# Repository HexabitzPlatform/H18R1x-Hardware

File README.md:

# H18R1x-Hardware

Hexabitz Dual H-Bridge Motor Driver Module Hardware Design

Redesign this module using the STM32G0B1CEU6 MCU and STSPIN948. Use the EVSPIN948 as a reference.

This design must use three hexagons with a 2-layer PCB stack-up.

Schematic: 
PCB:

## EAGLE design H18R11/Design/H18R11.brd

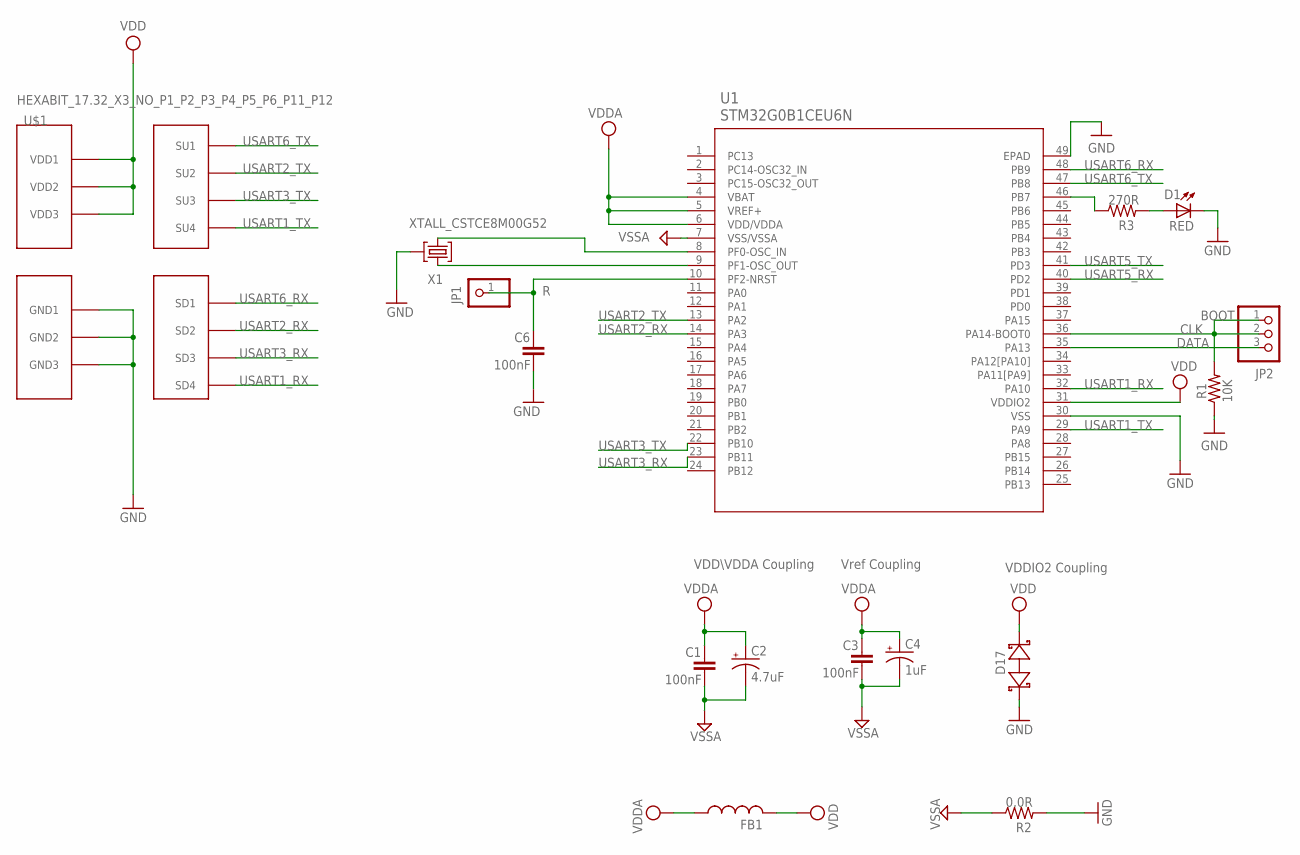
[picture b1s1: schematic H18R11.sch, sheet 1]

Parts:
C1, C3, C6: 100nF; C-0603
C2: 4.7uF; C-0805-POL
C4: 1uF; C-0805-POL
D1: RED; VLMS1300-GS08; MPN VLMS1300-GS08
D17: BOURNS_CDSOD323-T03SCBOURNS_CDSOD323-T03SC_0_0; BOURNS_CDSOD323-T03SC_0
FB1: FB-0603
JP1: R; 1X01
JP2: PINHD-1X3; 1X03
R1: 10K; R-0603
R2: 0.0R; R-0603
R3: 270R; R-0603
U1: STM32G0B1CEU6N; HEXABITZ_ICS_QFN_B1CEU6_STM-L
U$1: HEXABIT_17.32_X3_NO_P1_P2_P3_P4_P5_P6_P11_P12
X1: XTALL_CSTCE8M00G52

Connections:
CLK: JP2.1, JP2.2, R1.2, U1.36 (PA14-BOOT0)
DATA: JP2.3, U1.35 (PA13)
GND: C6.2, D1.C, D17.1 (A), R1.1, R2.2, U1.30 (VSS), U1.49 (EPAD), U$1.PAD_PD12 (GND1), U$1.PAD_PD17 (GND2), U$1.PAD_PD19 (GND3), X1.P$2 (2); also elsewhere on the board
unnamed: D1.A, R3.2
unnamed: R3.1, U1.46 (PB7)
unnamed: U1.9 (PF1-OSC_OUT), X1.P$1 (1)
unnamed: U1.8 (PF0-OSC_IN), X1.P$3 (3)
unnamed: C6.1, JP1.1, U1.10 (PF2-NRST)
USART1_RX: U1.32 (PA10), U$1.PAD_PD8 (SD4)
USART1_TX: U1.29 (PA9), U$1.PAD_PU8 (SU4)
USART2_RX: U1.14 (PA3), U$1.PAD_PD1 (SD2)
USART2_TX: U1.13 (PA2), U$1.PAD_PU1 (SU2)
USART3_RX: U1.23 (PB11), U$1.PAD_PD2 (SD3)
USART3_TX: U1.22 (PB10), U$1.PAD_PU2 (SU3)
USART5_RX: U1.40 (PD2)
USART5_TX: U1.41 (PD3)
USART6_RX: U1.48 (PB9), U$1.PAD_PD3 (SD1)
USART6_TX: U1.47 (PB8), U$1.PAD_PU3 (SU1)
VDD: D17.2 (C), FB1.2, U1.31 (VDDIO2), U$1.PAD_PU12 (VDD1), U$1.PAD_PU17 (VDD2), U$1.PAD_PU19 (VDD3); also elsewhere on the board
VDDA: C1.1, C2.1 (+), C3.1, C4.1 (+), FB1.1, U1.4 (VBAT), U1.5 (VREF+), U1.6 (VDD/VDDA)
VSSA: C1.2, C2.2 (-), C3.2, C4.2 (-), R2.1, U1.7 (VSS/VSSA); also elsewhere on the board

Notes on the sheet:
Vref Coupling
VDDIO2 Coupling
VDD\VDDA Coupling
BOOT

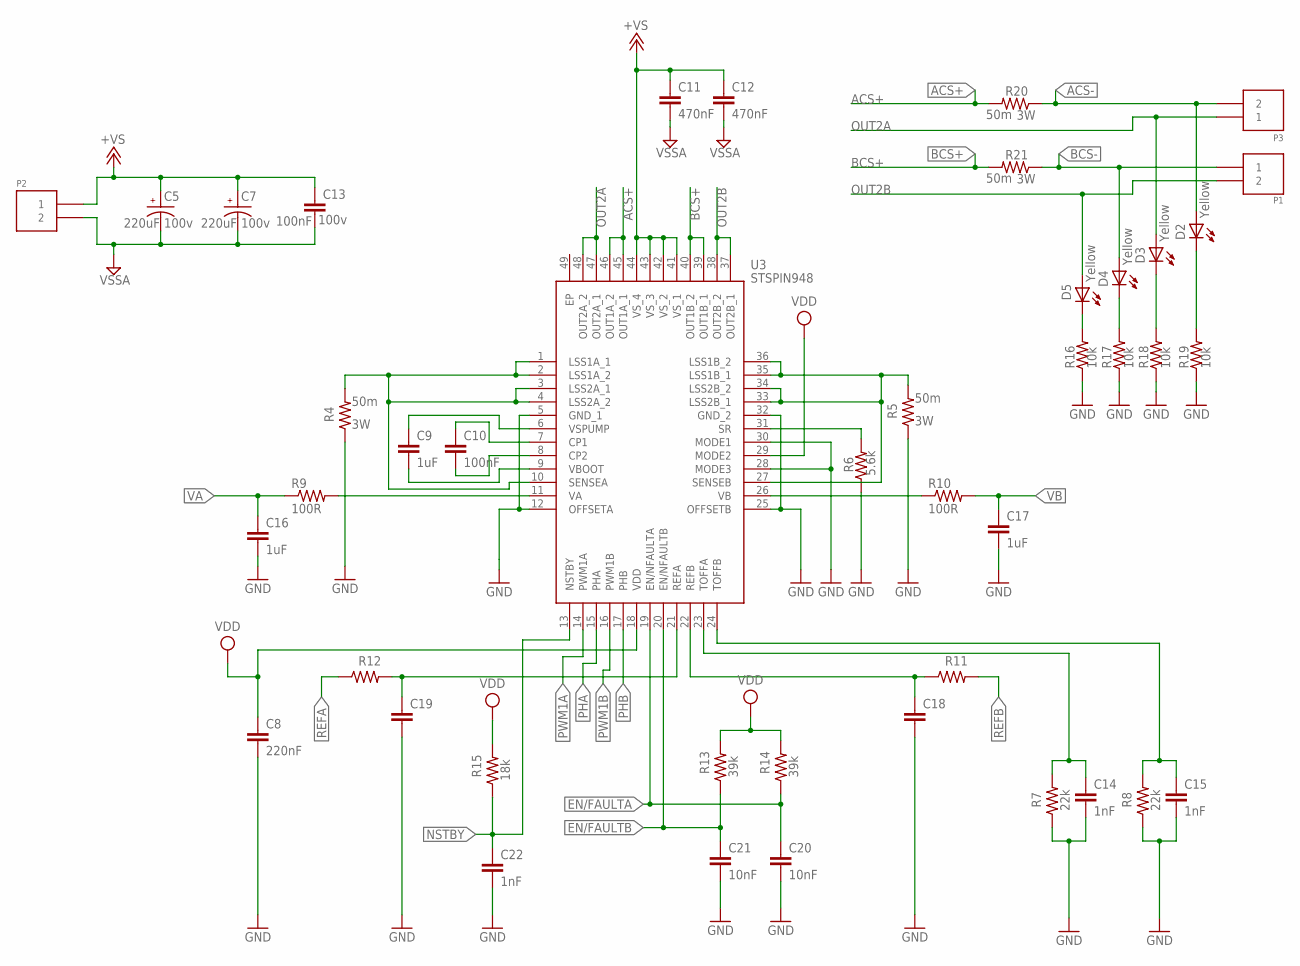
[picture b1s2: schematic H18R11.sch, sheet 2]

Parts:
C5, C7: 220uF; CAPPRD500W60D1250H2500
C8: 220nF; C-0603
C9, C16, C17: 1uF; C-0603
C10: 100nF; C-0603
C11, C12: 470nF; C-0603
C13: 100nF; C-0603; VOLTAGE_RATING 100v
C14, C15, C22: 1nF; C-0603
C18, C19: C-0603
C20, C21: 10nF; C-0603
D2: Yellow; VLMS1300-GS08; MPN VLMS1300-GS08
D3, D4, D5: Yellow; VLMS1300-GS08
P1, P2, P3: 1546111-2
R4, R5, R20, R21: 50m; R2512; MPN CRA2512-FZ-R050ELF
R6: 5.6k; R-0603
R7, R8: 22k; R-0603
R9, R10: 100R; R-0603
R11, R12: R-0603
R13, R14: 39k; R-0603
R15: 18k; R-0603
R16, R17, R18, R19: 10k; R-0805
U3: STSPIN948; QFN50P700X700X105-49N

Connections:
+VS: C5.P, C7.P, C11.1, C12.1, C13.1, P2.1, U3.41 (VS_1), U3.42 (VS_2), U3.43 (VS_3), U3.44 (VS_4)
ACS+: R20.2, U3.45 (OUT1A_1), U3.46 (OUT1A_2); also elsewhere on the board
ACS-: D2.A, P3.2, R20.1; also elsewhere on the board
BCS+: R21.2, U3.39 (OUT1B_1), U3.40 (OUT1B_2); also elsewhere on the board
BCS-: D4.A, P1.1, R21.1; also elsewhere on the board
EN/FAULTA: C20.1, R14.1, U3.19 (EN/NFAULTA)
EN/FAULTB: C21.1, R13.1, U3.20 (EN/NFAULTB)
GND: C8.2, C14.2, C15.2, C16.2, C17.2, C18.2, C19.2, C20.2, C21.2, C22.2, R4.1, R5.1, R6.1, R7.1, R8.1, R16.1, R17.1, R18.1, R19.1, U3.5 (GND_1), U3.12 (OFFSETA), U3.25 (OFFSETB), U3.28 (MODE3), U3.30 (MODE1), U3.32 (GND_2); also elsewhere on the board
unnamed: C9.1, U3.6 (VSPUMP)
unnamed: C9.2, U3.9 (VBOOT)
unnamed: C10.1, U3.7 (CP1)
unnamed: C10.2, U3.8 (CP2)
unnamed: R4.2, U3.1 (LSS1A_1), U3.2 (LSS1A_2), U3.3 (LSS2A_1), U3.4 (LSS2A_2), U3.10 (SENSEA)
unnamed: R5.2, U3.27 (SENSEB), U3.33 (LSS2B_1), U3.34 (LSS2B_2), U3.35 (LSS1B_1), U3.36 (LSS1B_2)
unnamed: R6.2, U3.31 (SR)
unnamed: C14.1, R7.2, U3.23 (TOFFA)
unnamed: R9.2, U3.11 (VA)
unnamed: R10.1, U3.26 (VB)
unnamed: C15.1, R8.2, U3.24 (TOFFB)
unnamed: C19.1, R12.2, U3.21 (REFA)
unnamed: C18.1, R11.1, U3.22 (REFB)
unnamed: D3.C, R18.2
unnamed: D5.C, R16.2
unnamed: D4.C, R17.2
unnamed: D2.C, R19.2
NSTBY: C22.1, R15.1, U3.13 (NSTBY)
OUT2A: D3.A, P3.1, U3.47 (OUT2A_1), U3.48 (OUT2A_2)
OUT2B: D5.A, P1.2, U3.37 (OUT2B_1), U3.38 (OUT2B_2)
PHA: U3.15 (PHA)
PHB: U3.17 (PHB)
PWM1A: U3.14 (PWM1A)
PWM1B: U3.16 (PWM1B)
REFA: R12.1
REFB: R11.2
VA: C16.1, R9.1
VB: C17.1, R10.2
VDD: C8.1, R13.2, R14.2, R15.2, U3.18 (VDD), U3.29 (MODE2); also elsewhere on the board
VSSA: C5.N, C7.N, C11.2, C12.2, C13.2, P2.2; also elsewhere on the board

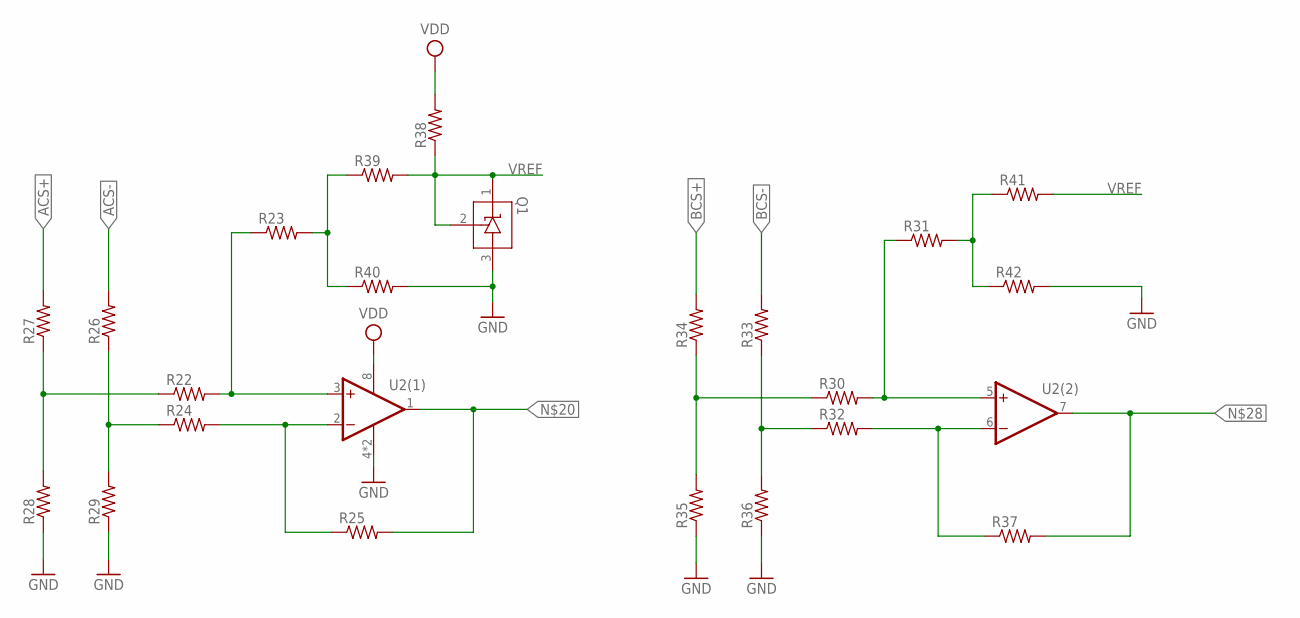
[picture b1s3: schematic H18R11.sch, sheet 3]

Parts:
Q1: TL431QDBZR,215; SOT23_TO-236AB_NEX
R22, R23, R24, R25, R26, R27, R28, R29, R30, R31, R32, R33, R34, R35, R36, R37, R38, R39, R40, R41, R42: R-0402
U2: TSV772IQ2T_SEPARATED_SYMBOLSSON50P200X200X60-9N; SON50P200X200X60-9N

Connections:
ACS+: R27.2; also elsewhere on the board
ACS-: R26.2; also elsewhere on the board
BCS+: R34.2; also elsewhere on the board
BCS-: R33.2; also elsewhere on the board
GND: Q1.3, R28.1, R29.1, R35.1, R36.1, R40.2, R42.2, U2.4 (V-), U2.9 (V-); also elsewhere on the board
unnamed: R25.2, U2.1 (OUT)
unnamed: R24.2, R25.1, U2.2 (-IN)
unnamed: R31.2, R41.1, R42.1
unnamed: R24.1, R26.1, R29.2
unnamed: R22.1, R27.1, R28.2
unnamed: R37.2, U2.7 (OUT)
unnamed: R32.2, R37.1, U2.6 (-IN)
unnamed: R32.1, R33.1, R36.2
unnamed: R30.1, R34.1, R35.2
unnamed: R22.2, R23.1, U2.3 (+IN)
unnamed: R23.2, R39.1, R40.1
VDD: R38.2, U2.8 (V+); also elsewhere on the board
VREF: Q1.1, Q1.2, R30.2, R31.1, R38.1, R39.2, R41.2, U2.5 (+IN)

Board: 4 copper layers, 82 parts (35 on the bottom side), 60 nets, no tracks yet.

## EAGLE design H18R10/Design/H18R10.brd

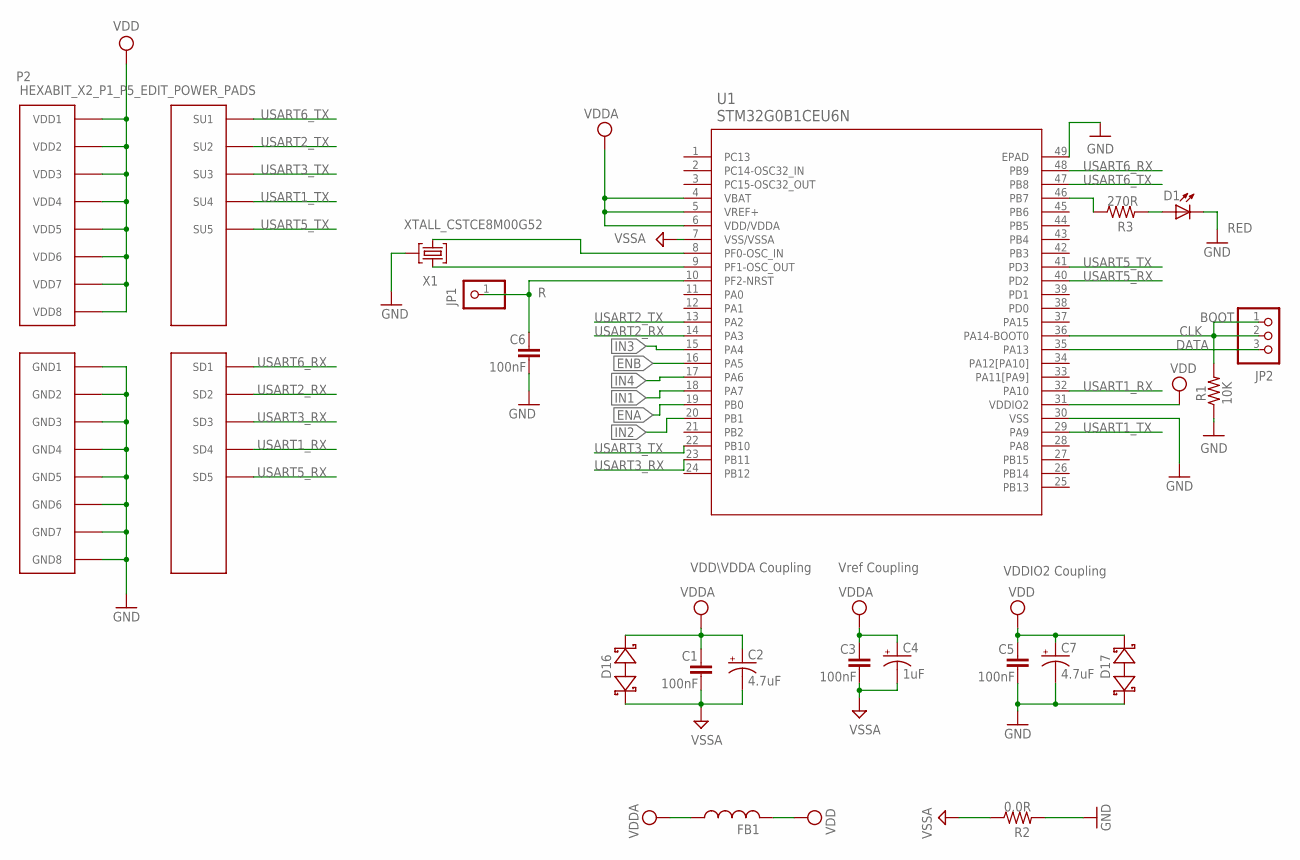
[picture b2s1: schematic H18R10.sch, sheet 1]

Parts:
C1, C3, C5, C6: 100nF; C-0603
C2, C7: 4.7uF; C-0805-POL
C4: 1uF; C-0805-POL
D1: RED; VLMS1300-GS08; MPN VLMS1300-GS08
D16, D17: BOURNS_CDSOD323-T03SCBOURNS_CDSOD323-T03SC_0_0; BOURNS_CDSOD323-T03SC_0
FB1: FB-0603
JP1: R; 1X01
JP2: PINHD-1X3; 1X03
P2: HEXABIT_X2_P1_P5_EDIT_POWER_PADS
R1: 10K; R-0603
R2: 0.0R; R-0603
R3: 270R; R-0603
U1: STM32G0B1CEU6N; HEXABITZ_ICS_QFN_B1CEU6_STM-L
X1: XTALL_CSTCE8M00G52

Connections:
CLK: JP2.1, JP2.2, R1.2, U1.36 (PA14-BOOT0)
DATA: JP2.3, U1.35 (PA13)
ENA: U1.19 (PB0); also elsewhere on the board
ENB: U1.16 (PA5); also elsewhere on the board
GND: C5.2, C6.2, C7.2 (-), D1.C, D17.1 (A), P2.PAD_PD11 (GND1), P2.PAD_PD12 (GND2), P2.PAD_PD13 (GND3), P2.PAD_PD14 (GND4), P2.PAD_PD17 (GND5), P2.PAD_PD18 (GND6), P2.PAD_PD19 (GND7), P2.PAD_PD20 (GND8), R1.1, R2.2, U1.30 (VSS), U1.49 (EPAD), X1.P$2 (2)
IN1: U1.18 (PA7); also elsewhere on the board
IN2: U1.20 (PB1); also elsewhere on the board
IN3: U1.15 (PA4); also elsewhere on the board
IN4: U1.17 (PA6); also elsewhere on the board
unnamed: D1.A, R3.2
unnamed: R3.1, U1.46 (PB7)
unnamed: U1.9 (PF1-OSC_OUT), X1.P$1 (1)
unnamed: U1.8 (PF0-OSC_IN), X1.P$3 (3)
unnamed: C6.1, JP1.1, U1.10 (PF2-NRST)
USART1_RX: P2.PAD_PD4 (SD4), U1.32 (PA10)
USART1_TX: P2.PAD_PU4 (SU4), U1.29 (PA9)
USART2_RX: P2.PAD_PD2 (SD2), U1.14 (PA3)
USART2_TX: P2.PAD_PU2 (SU2), U1.13 (PA2)
USART3_RX: P2.PAD_PD3 (SD3), U1.23 (PB11)
USART3_TX: P2.PAD_PU3 (SU3), U1.22 (PB10)
USART5_RX: P2.PAD_PD5 (SD5), U1.40 (PD2)
USART5_TX: P2.PAD_PU5 (SU5), U1.41 (PD3)
USART6_RX: P2.PAD_PD1 (SD1), U1.48 (PB9)
USART6_TX: P2.PAD_PU1 (SU1), U1.47 (PB8)
VDD: C5.1, C7.1 (+), D17.2 (C), FB1.2, P2.PAD_PU11 (VDD1), P2.PAD_PU12 (VDD2), P2.PAD_PU13 (VDD3), P2.PAD_PU14 (VDD4), P2.PAD_PU17 (VDD5), P2.PAD_PU18 (VDD6), P2.PAD_PU19 (VDD7), P2.PAD_PU20 (VDD8), U1.31 (VDDIO2)
VDDA: C1.1, C2.1 (+), C3.1, C4.1 (+), D16.2 (C), FB1.1, U1.4 (VBAT), U1.5 (VREF+), U1.6 (VDD/VDDA); also elsewhere on the board
VSSA: C1.2, C2.2 (-), C3.2, C4.2 (-), D16.1 (A), R2.1, U1.7 (VSS/VSSA); also elsewhere on the board

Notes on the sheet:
Vref Coupling
VDDIO2 Coupling
VDD\VDDA Coupling
BOOT

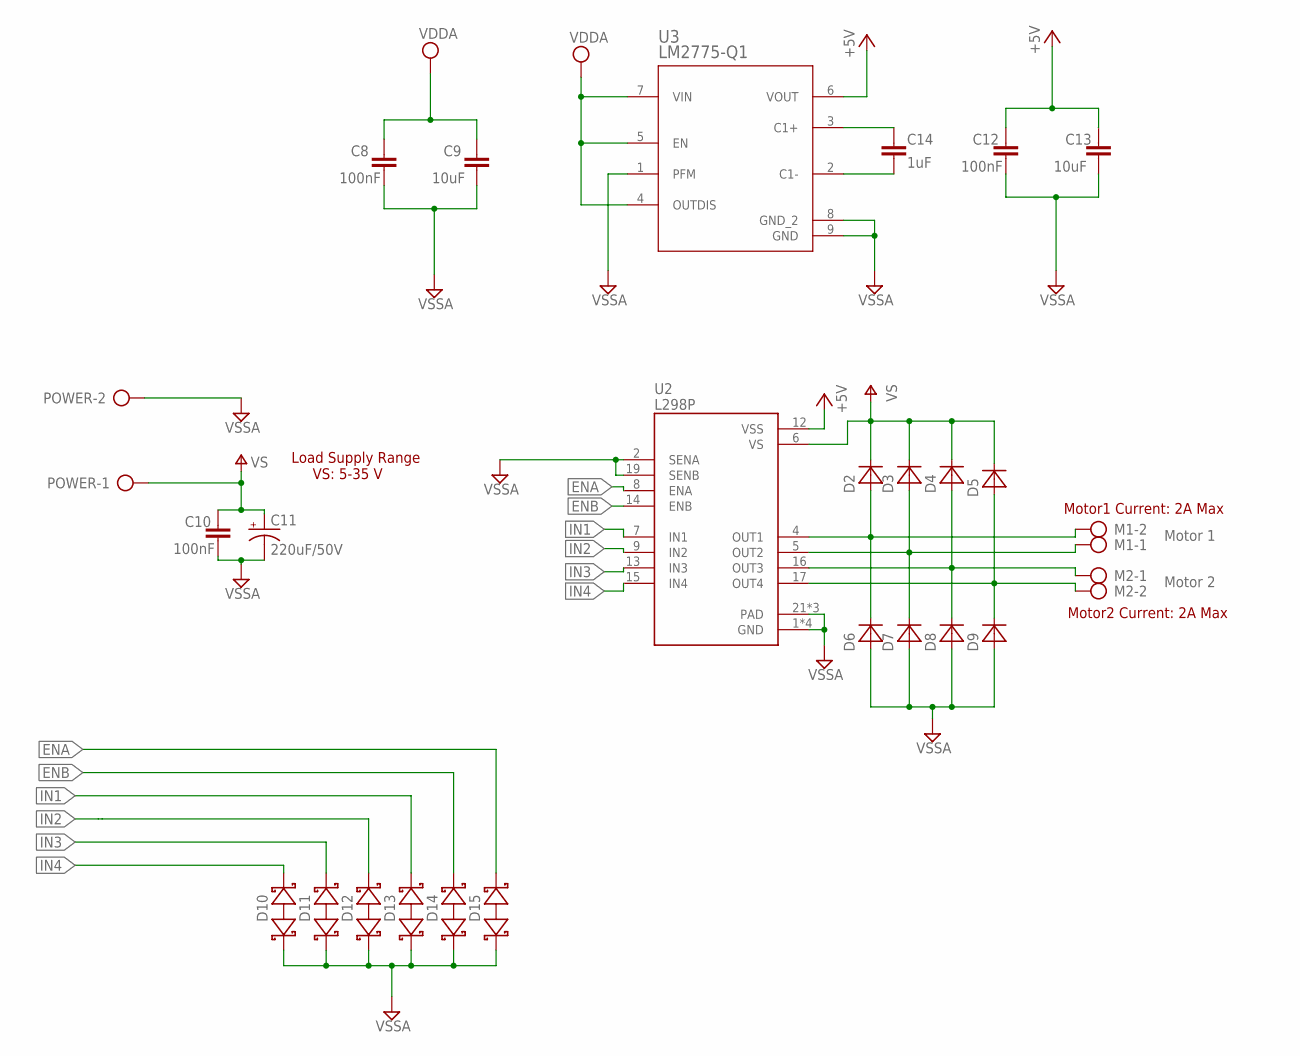
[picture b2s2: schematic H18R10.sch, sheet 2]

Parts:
C8, C10, C12: 100nF; C-0603
C9, C13: 10uF; C-0603
C11: 220uF/50V; TT5D10
C14: 1uF; C-0603
D2, D3, D4, D5, D6, D7, D8, D9: DIOD-SOD-123; SOD123
D10, D11, D12, D13, D14, D15: BOURNS_CDSOD323-T03SCBOURNS_CDSOD323-T03SC_0_0; BOURNS_CDSOD323-T03SC_0
M1, M2: AK500/2
POWER: AK500/2
U2: L298P; SOIC127P1420X360-20N
U3: LM2775-Q1; DSG0008A

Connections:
+5V: C12.1, C13.1, U2.12 (VSS), U3.6 (VOUT)
ENA: D15.2 (C), U2.8 (ENA); also elsewhere on the board
ENB: D14.2 (C), U2.14 (ENB); also elsewhere on the board
IN1: D13.2 (C), U2.7 (IN1); also elsewhere on the board
IN2: D12.2 (C), U2.9 (IN2); also elsewhere on the board
IN3: D11.2 (C), U2.13 (IN3); also elsewhere on the board
IN4: D10.2 (C), U2.15 (IN4); also elsewhere on the board
unnamed: C14.2, U3.2 (C1-)
unnamed: C14.1, U3.3 (C1+)
unnamed: D5.1 (A), D9.2 (C), M2.2, U2.17 (OUT4)
unnamed: D3.1 (A), D7.2 (C), M1.1, U2.5 (OUT2)
unnamed: D4.1 (A), D8.2 (C), M2.1, U2.16 (OUT3)
unnamed: D2.1 (A), D6.2 (C), M1.2, U2.4 (OUT1)
V+: C10.1, C11.+, D2.2 (C), D3.2 (C), D4.2 (C), D5.2 (C), POWER.1, U2.6 (VS)
VDDA: C8.1, C9.1, U3.4 (OUTDIS), U3.5 (EN), U3.7 (VIN); also elsewhere on the board
VSSA: C8.2, C9.2, C10.2, C11.-, C12.2, C13.2, D6.1 (A), D7.1 (A), D8.1 (A), D9.1 (A), D10.1 (A), D11.1 (A), D12.1 (A), D13.1 (A), D14.1 (A), D15.1 (A), POWER.2, U2.1 (GND), U2.2 (SENA), U2.10 (GND), U2.11 (GND), U2.19 (SENB), U2.20 (GND), U2.21 (PAD), U2.22 (PAD), U2.23 (PAD), U3.1 (PFM), U3.8 (GND_2), U3.9 (GND); also elsewhere on the board

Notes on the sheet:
Motor 1
Motor 2
Load Supply Range VS: 5-35 V
Motor1 Current: 2A Max
Motor2 Current: 2A Max

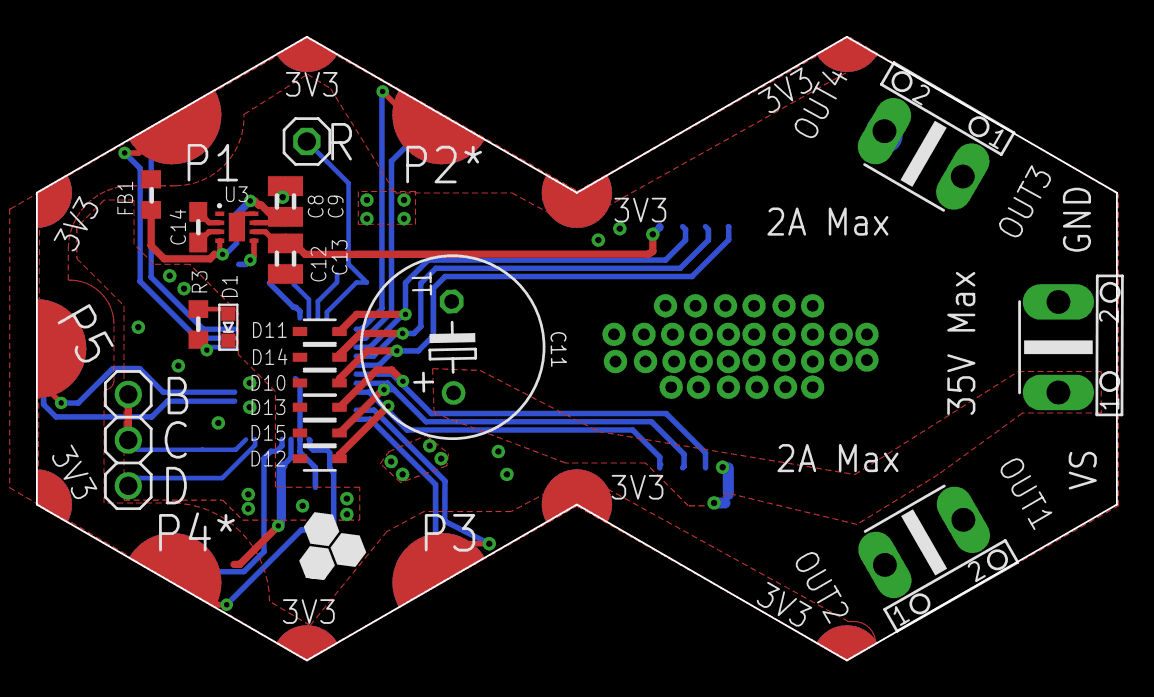
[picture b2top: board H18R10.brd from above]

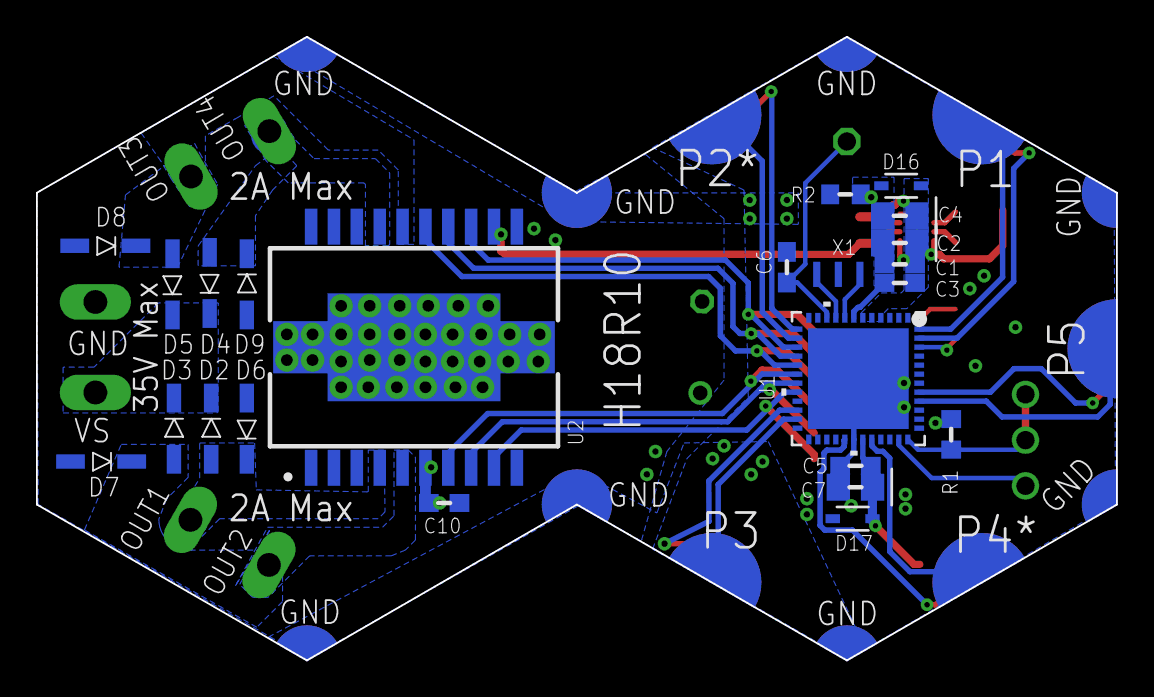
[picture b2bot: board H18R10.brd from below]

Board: 2 copper layers, 60.0 x 34.6 mm, 45 parts (23 on the bottom side), 35 nets.

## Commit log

2022-08-19 Add .gitignore file
2022-08-19 Edited README.md file
2022-08-23 no message
2022-08-24 Edit Readme file.
2022-08-24 Editing Readme file
2023-02-16 -Adding a heatsink - replace the MC7805 with LM2775 IC
2023-11-26 -Improving the layout desin and adding TVSs at the MCU GPIOs that connected to the driver IC inputs, and across its supply pins all to increase the imunity against the high spikes.
2024-12-17 - All cleaned and ready to set a new design.
2024-12-18 - Initial schematic design.
2025-01-22 - New schematic design - Initial Layout setup - Generated documentation
2025-10-16 The Altium template has been added.
2025-11-19 new schematic in f/b
2025-11-21 new schematic in f/b2
2025-11-25 new schematic in f/b3
2025-11-26 new schematic in f/b4
2025-11-29 new pcb

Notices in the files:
parts and their libraries:
HEXABITZ_ICs: COPYRIGHT: Copyright (C) 2022 Ultra Librarian. All rights reserved.
